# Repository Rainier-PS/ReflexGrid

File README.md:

# ReflexGrid

> ReflexGrid is a minimalist reflex and movement game played on a 2×2 LED grid with 4 directional buttons. Test your reaction speed and stay alive. Small board. Big tension.

## What is ReflexGrid?

ReflexGrid is an ultra-compact, open-source game board powered by a Seeed Xiao RP2040. It features only 4 mechanical switches and 4 LEDs in a 2×2 layout. ReflexGrid runs a fast-paced **LED dodging game** where players must react quickly to shifting danger zones or face a total wipeout.

More mini-games and expansions are planned in future updates.

## Images

### Schematic  

### PCB Layout  

### ReflexGrid Board - Front  

### ReflexGrid Board - Back  

## Features

- Reflex-based dodging game with increasing difficulty
- Player-controlled movement using 4-direction buttons
- 2×2 LED grid system with live danger indicators
- Clean, readable Arduino code
- Built-in game reset and failure animation
- Fully self-contained, no display or computer needed

## How to Play

- You control a single LED (the "player") using ↑ ↓ ← → buttons.
- A **danger tile** (flashing LED) appears randomly.
- You must **move away from the danger tile** before the timer runs out.
- Survive, and the game speeds up for the next round.
- Stay on the danger tile too long? All LEDs flash → Game Over.

### LED State Reference

| State               | LED Behavior            |
|--------------------|-------------------------|
| Player position     | Solid ON                |
| Danger tile         | Blinking (~5 Hz)        |
| Player on danger    | Lose after ~2 seconds   |
| Game over           | All 4 LEDs blink rapidly|
| New round           | LED moves, game speeds up |

### Button–LED Layout (Top View)

```

[UP]
  ↑
                     [LEFT] ←       → [RIGHT]
  ↓
[DOWN]

```

### LED Grid Layout (Top View)

| Grid Position | LED | GPIO | Location       |
|---------------|-----|------|----------------|
| [0,0]         | 1   | 29   | Upper Left     |
| [1,0]         | 2   | 27   | Upper Right    |
| [0,1]         | 3   | 7    | Lower Left     |
| [1,1]         | 4   | 6    | Lower Right    |

## Future Plans

- Additional game modes (memory, pattern match, chase)
- USB HID gamepad mode with feedback

## Getting Started

### 1. Flash the Code

Upload the `ReflexGrid.ino` sketch to your board using the Arduino IDE with RP2040 support installed.

### 2. Wiring

| Function    | GPIO Pin | Notes             |
|-------------|----------|-------------------|
| Button UP   | GPIO26   | Internal pull-up  |
| Button DOWN | GPIO28   | Internal pull-up  |
| Button LEFT | GPIO4    | Internal pull-up  |
| Button RIGHT| GPIO3    | Internal pull-up  |
| LED UL      | GPIO29   | Upper Left        |
| LED UR      | GPIO27   | Upper Right       |
| LED LL      | GPIO7    | Lower Left        |
| LED LR      | GPIO6    | Lower Right       |

## Advanced Notes

- **GND Test Pad**  
  A dedicated exposed GND pad is included on the PCB for easy multimeter probing and diagnostics. Useful during debugging or for adding temporary modules or sensors.

- **Dual Pin Headers for Xiao**  
  The Xiao RP2040 footprint includes **double/duplicate pin holes**, one for standard mounting, and another inline set for breakout or jumper wiring. This allows GridCore to be used not only as a game system, but also as a **hackable Xiao devboard** for rapid prototyping.

> **Note**  
> This board passes both ERC and DRC checks and meets all Pathfinder hardware submission standards.
> Hackatime records for the Kicad PCB file goes by the name DIYGamepad and Arduino firmware file goes by the name ReflexGrid. 

---

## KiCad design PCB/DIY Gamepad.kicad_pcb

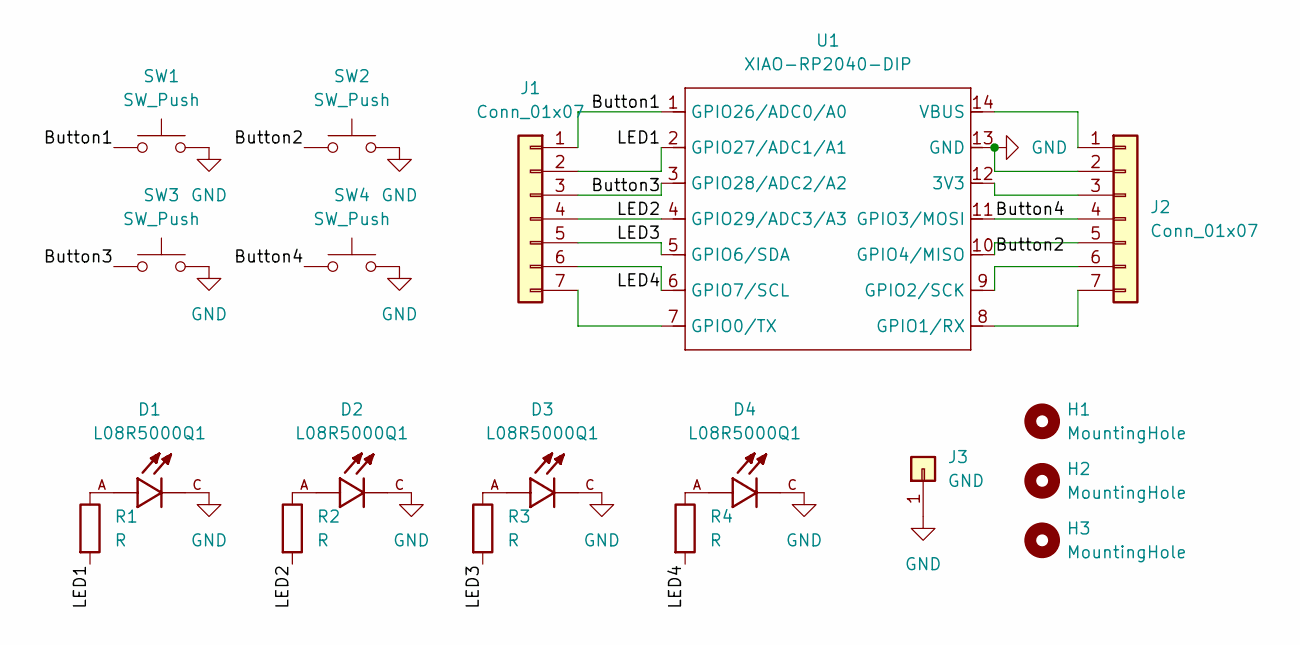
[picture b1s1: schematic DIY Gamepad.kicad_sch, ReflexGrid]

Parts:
D1, D2, D3, D4: L08R5000Q1; LEDRD254W57D500H1070; PARTREV NA
H1, H2, H3: MountingHole; MountingHole_3.2mm_M3
J1, J2: Conn_01x07; PinHeader_1x07_P2.54mm_Vertical
J3: GND; TestPoint_THTPad_D1.5mm_Drill0.7mm
R1, R2, R3, R4: R; R_Axial_DIN0204_L3.6mm_D1.6mm_P5.08mm_Horizontal
SW1, SW2, SW3, SW4: SW_Push; SW_Cherry_MX_1.00u_PCB
U1: XIAO-RP2040-DIP

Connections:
/Button1: J1.1, SW1.1, U1.1 (GPIO26/ADC0/A0)
/Button2: J2.5, SW2.1, U1.10 (GPIO4/MISO)
/Button3: J1.3, SW3.1, U1.3 (GPIO28/ADC2/A2)
/Button4: J2.4, SW4.1, U1.11 (GPIO3/MOSI)
/LED1: J1.2, R1.2, U1.2 (GPIO27/ADC1/A1)
/LED2: J1.4, R2.2, U1.4 (GPIO29/ADC3/A3)
/LED3: J1.5, R3.2, U1.5 (GPIO6/SDA)
/LED4: J1.6, R4.2, U1.6 (GPIO7/SCL)
GND: D1.C, D2.C, D3.C, D4.C, J2.2, J3.1, SW1.2, SW2.2, SW3.2, SW4.2, U1.13 (GND)
unnamed: D1.A, R1.1
unnamed: D2.A, R2.1
unnamed: D3.A, R3.1
unnamed: D4.A, R4.1
unnamed: J1.7, U1.7 (GPIO0/TX)
unnamed: J2.1, U1.14 (VBUS)
unnamed: J2.3, U1.12 (3V3)
unnamed: J2.6, U1.9 (GPIO2/SCK)
unnamed: J2.7, U1.8 (GPIO1/RX)

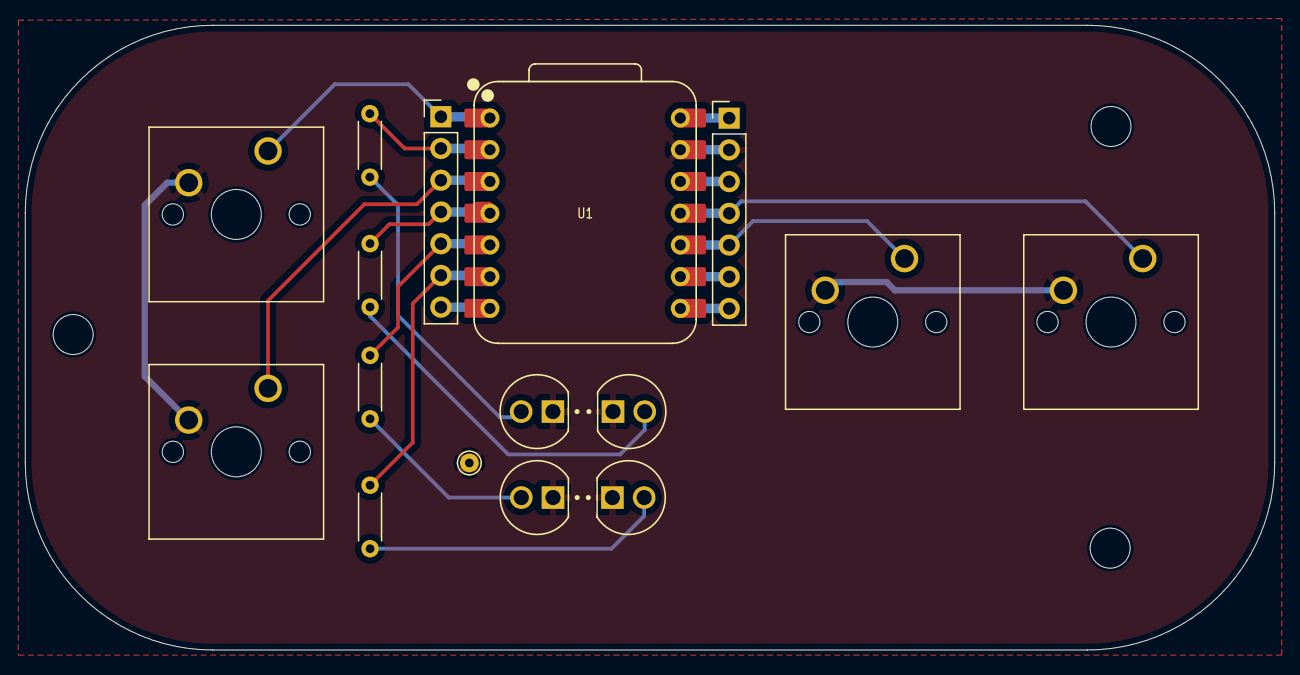
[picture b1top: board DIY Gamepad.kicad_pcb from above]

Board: 2 copper layers, 100.0 x 50.0 mm, 19 parts (0 on the bottom side), 18 nets.

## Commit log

2025-07-31 Create Temp
2025-07-31 Update and rename Temp to Temp
2025-12-30 Refactor danger logic and enhance game features
    Refactored danger handling and added LED blinking functionality. Introduced score tracking and improved input handling.
